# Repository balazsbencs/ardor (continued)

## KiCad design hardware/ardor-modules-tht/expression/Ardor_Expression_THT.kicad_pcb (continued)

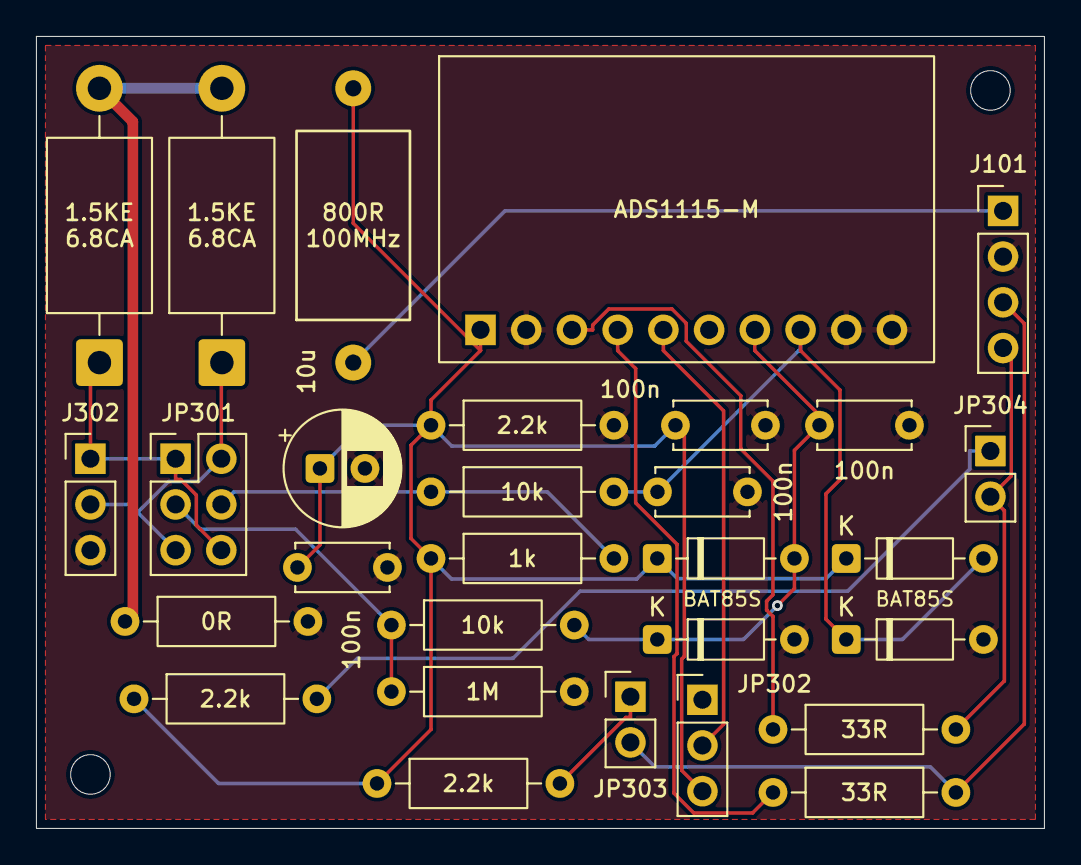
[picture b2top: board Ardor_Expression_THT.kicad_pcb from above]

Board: 2 copper layers, 56.0 x 44.0 mm, 31 parts (0 on the bottom side), 17 nets.

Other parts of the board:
H1, H2: MountingHole_2.2mm_M2

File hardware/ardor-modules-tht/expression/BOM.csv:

Reference,Value,Footprint,Purchasing specification,Assembly
J302,"PASSIVE PEDAL INPUT / EXCITATION
OUTPUT",Connector_PinHeader_2.54mm:PinHeader_1x03_P2.54mm_Vertical,PinHeader_1x03_P2.54mm_Vertical,THT manual
J101,3V3 POWER INPUT + I2C TO HOST,Connector_PinHeader_2.54mm:PinHeader_1x04_P2.54mm_Vertical,PinHeader_1x04_P2.54mm_Vertical,THT manual
JP301,JUMPER ONLY: PEDAL POLARITY,Connector_PinHeader_2.54mm:PinHeader_2x03_P2.54mm_Vertical,PinHeader_2x03_P2.54mm_Vertical,THT manual
FB101,800R@100MHz / WE 7427501,Ardor_THT:Ferrite_WE_7427501_P15.24mm,Wurth Elektronik 7427501,THT manual
C101,10u / 25V polarized,Capacitor_THT:CP_Radial_D6.3mm_P2.50mm,"Radial electrolytic 10uF 25V, D<=6.3mm P2.5mm",THT manual
C102,100n / 50V X7R,Capacitor_THT:C_Disc_D5.0mm_W2.5mm_P5.00mm,"100nF 50V X7R radial, 5mm lead pitch",THT manual
R301,1kR / 1% 0.25W,Resistor_THT:R_Axial_DIN0207_L6.3mm_D2.5mm_P10.16mm_Horizontal,Axial metal film 1kΩ 1% 0.25W,THT manual
R302,10kR / 1% 0.25W,Resistor_THT:R_Axial_DIN0207_L6.3mm_D2.5mm_P10.16mm_Horizontal,Axial metal film 10kΩ 1% 0.25W,THT manual
R303,1MR / 1% 0.25W,Resistor_THT:R_Axial_DIN0207_L6.3mm_D2.5mm_P10.16mm_Horizontal,Axial metal film 1MΩ 1% 0.25W,THT manual
C301,100n / 50V X7R,Capacitor_THT:C_Disc_D5.0mm_W2.5mm_P5.00mm,"100nF 50V X7R radial, 5mm lead pitch",THT manual
R304,10kR / 1% 0.25W,Resistor_THT:R_Axial_DIN0207_L6.3mm_D2.5mm_P10.16mm_Horizontal,Axial metal film 10kΩ 1% 0.25W,THT manual
C302,100n / 50V X7R,Capacitor_THT:C_Disc_D5.0mm_W2.5mm_P5.00mm,"100nF 50V X7R radial, 5mm lead pitch",THT manual
U301,ADS1115-M,Ardor_THT:ADS1115_M_HESTORE_10041798,ADS1115-M (HESTORE 100.417.98),Preassembled module; THT sockets
C303,100n / 50V X7R,Capacitor_THT:C_Disc_D5.0mm_W2.5mm_P5.00mm,"100nF 50V X7R radial, 5mm lead pitch",THT manual
R307,2.2kR / 1% 0.25W,Resistor_THT:R_Axial_DIN0207_L6.3mm_D2.5mm_P10.16mm_Horizontal,Axial metal film 2.2kΩ 1% 0.25W,THT manual
D303,BAT85S,Diode_THT:D_DO-35_SOD27_P7.62mm_Horizontal,Vishay BAT85S-TAP,THT manual
D304,BAT85S,Diode_THT:D_DO-35_SOD27_P7.62mm_Horizontal,Vishay BAT85S-TAP,THT manual
D305,BAT85S,Diode_THT:D_DO-35_SOD27_P7.62mm_Horizontal,Vishay BAT85S-TAP,THT manual
D306,BAT85S,Diode_THT:D_DO-35_SOD27_P7.62mm_Horizontal,Vishay BAT85S-TAP,THT manual
R305,33R / 1% 0.25W,Resistor_THT:R_Axial_DIN0207_L6.3mm_D2.5mm_P10.16mm_Horizontal,Axial metal film 33Ω 1% 0.25W,THT manual
R306,33R / 1% 0.25W,Resistor_THT:R_Axial_DIN0207_L6.3mm_D2.5mm_P10.16mm_Horizontal,Axial metal film 33Ω 1% 0.25W,THT manual
JP302,JUMPER ONLY: ADC ADDRESS,Connector_PinHeader_2.54mm:PinHeader_1x03_P2.54mm_Vertical,PinHeader_1x03_P2.54mm_Vertical,THT manual
JP303,JUMPER ONLY: SDA PULLUP,Connector_PinHeader_2.54mm:PinHeader_1x02_P2.54mm_Vertical,PinHeader_1x02_P2.54mm_Vertical,THT manual
JP304,JUMPER ONLY: SCL PULLUP,Connector_PinHeader_2.54mm:PinHeader_1x02_P2.54mm_Vertical,PinHeader_1x02_P2.54mm_Vertical,THT manual
R308,2.2kR / 1% 0.25W,Resistor_THT:R_Axial_DIN0207_L6.3mm_D2.5mm_P10.16mm_Horizontal,Axial metal film 2.2kΩ 1% 0.25W,THT manual
R309,2.2kR / 1% 0.25W,Resistor_THT:R_Axial_DIN0207_L6.3mm_D2.5mm_P10.16mm_Horizontal,Axial metal film 2.2kΩ 1% 0.25W,THT manual
D301,1.5KE6.8CA,Ardor_THT:D_TVS_DC_1.5KE_P15.24mm,DC Components 1.5KE6.8CA (HESTORE 100.430.71),THT manual
D302,1.5KE6.8CA,Ardor_THT:D_TVS_DC_1.5KE_P15.24mm,DC Components 1.5KE6.8CA (HESTORE 100.430.71),THT manual
R101,0R / 1% 0.25W,Resistor_THT:R_Axial_DIN0207_L6.3mm_D2.5mm_P10.16mm_Horizontal,Axial metal film 0Ω 1% 0.25W,THT manual

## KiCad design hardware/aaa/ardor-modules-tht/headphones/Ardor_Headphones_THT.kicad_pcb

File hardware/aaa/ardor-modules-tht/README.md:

# Ardor hand-assembled function modules — T1

These are alternative KiCad 9 projects for the five [M1 production modules](../ardor-modules/README.md). Order bare PCBs and solder them with an ordinary iron. MIDI, mixer and line-out contain **only through-hole components**. The headphone board uses **one hand-solderable OPA1656ID SOIC-8**, with all supporting components through-hole. Expression uses a **purchased, preassembled ADS1115 breakout**: it contains SMD parts, but the builder only solders headers and sockets. The OPA1656 has exposed leads at 1.27 mm pitch and no underside pad; an ordinary iron and flux are sufficient. No hot-air tool or stencil is required.

| Project | PCB dimensions | Regulated supply budget | Assembly / differences from M1 |
|---|---|---|---|
| [MIDI input](midi-in/README.md) | 85 × 70 mm | 5 V / 10 mA + 3.3 V / 5 mA | DIP H11L1M; axial protection/filter parts |
| [Expression](expression/README.md) | 110 × 85 mm | 3.3 V / 15 mA | Socketed Adafruit 1085 **STEMMA QT revision**; same ADS1115 software |
| [Stereo/mono mixer](mixer/README.md) | 100 × 75 mm | 5 V / 10 mA | Socketed MCP6022-I/P; bipolar coupling capacitors |
| [Line output](line-out/README.md) | 115 × 85 mm | 5 V / 50 mA | MCP6022-I/P, through-hole relay, 2N3904 driver |
| [Stereo headphones](headphones/README.md) | 96 × 84 mm | 5 V / 150 mA | One OPA1656ID SOIC-8, THT supporting parts, DPDT relay mute |

All host and panel **connector pin assignments are the same as M1**. The larger boards and mounting holes are not mechanically interchangeable with M1. Each project has its own schematic, routed PCB, local libraries, manual BOM, connector guide, review drawings and bare-board Gerber/drill ZIP. Each module operates independently with an external host/audio source and the listed supplies. No carrier board or other Ardor module is required.

## Build choices

- Use 1% 0.25 W axial resistors, formed to 10.16 mm lead spacing, except headphone feedback resistors R651/R652: stand these upright at 2.54 mm pitch with short folded leads. R101 may be a wire link.
- On the headphone board, solder and inspect the OPA1656 SOIC-8 first; no IC socket or adapter is used. On the other boards, solder DIP sockets before fitting ICs. Match the IC notch to the socket and PCB pin-1 marking. The MIDI H11L1M uses a six-pin DIP footprint; an optional 7.62 mm-wide socket fits it.
- Use the capacitor dimensions and lead pitch in each BOM. The audio coupling capacitors marked **BIPOLAR** must be nonpolar electrolytics; ordinary polarized electrolytics are not substitutes. Polarized radial capacitors have pin 1 = positive and a `+` on the PCB. The can's stripe indicates negative.
- Use **bidirectional** DC Components **1.5KE6.8CA** protection diodes ([HESTORE 100.430.71](https://www.hestore.hu/prod_10043071.html)), formed to **15.24 mm** lead spacing. Either orientation is valid. MIDI D203/D204 retain **SA24CA-E3/54 at 10.16 mm pitch** for their higher-voltage protection function; do not fit 1.5KE6.8CA there. The `CA` suffix matters. Small-signal 1N4148 and BAT85S diodes are polarized: their band goes to the cathode, footprint pad 1.
- Filter beads are Würth 7427501 axial parts, formed to 15.24 mm spacing. Their RF characteristics and the axial TVS capacitance differ from M1; EMC/ESD equivalence is not claimed.
- Line/headphone enable drives a transistor base through 470 Ω. The host must source approximately **5 mA at 3.3 V HIGH**, rather than drive only a MOSFET gate. LOW or disconnected keeps the relay muted. Check the GPIO's drive capability.
- Fit standard 2.54 mm headers; panel DIN/TRS/TS sockets remain connected by wires. Read the module's pin table before wiring: different module types do not share a universal power pinout.

## Headphone tradeoff

The headphone board uses a modern dual OPA1656 audio op amp as the agreed hand-solderable SMD exception. It operates from regulated 5 V ±5% in an inverting circuit with nominal unloaded gain −0.5; both channels invert together. Its inputs stay at the filtered 2.5 V reference because the common-mode input range is restricted near the positive supply. Local feedback uses upright THT 10 kΩ resistors and 100 pF C0G capacitors. A 100 nF THT bypass sits close to U601. The remaining parts are THT.

Two 10 Ω output resistors sit outside the feedback loops, before the 470 µF DC-blocking capacitors. Calculated midband gain into 32 Ω is about −0.378, approximately 4.5 mW/channel for 1 Vrms input. This preserves the modest output level of the DIY alternative; it is not a measured clean-power rating. Use 32–300 Ω headphones, a source no greater than 1 Vrms, and begin at low host volume. Clean output, noise, cable-load stability and startup/switching transients remain bench-test items.
**Keep HP_ENABLE LOW for at least five seconds after the supply and audio are stable.** The 1 kΩ bleeders charge the output capacitors while the relay grounds the panel outputs. The board has no automatic timer: the host must provide this delay and mute before power-down. M1's timing may need adjustment. This relay mutes the output; it does not shut down the amplifiers or save their idle current.

## Files and validation

Open the `.kicad_pro` in the desired folder. Use `BOM.csv` plus `assembly/accessories.csv` for manual shopping and the ZIP under `assembly/` for a bare PCB order. Do not use M1's SMT BOM/CPL for these boards. Front silkscreen identifies every builder-fitted part; back silkscreen provides connector numbers and wiring legends. Native schematic PDFs and front/back/assembly views are under `review/`.

[Printable assembly overview](review/module-overview.pdf) · [All five schematics](review/schematics.pdf)

These are **unbuilt engineering prototypes**. CAD checks establish connectivity, geometry and the documented hand-assembly package choices; they do not establish measured audio quality, ESD performance or startup behavior. Each module guide includes commissioning steps. See [engineering review](review/REVIEW.md), [validation summary](review/validation-summary.json), [design regeneration](design/README.md) and [component sources and substitutions](SOURCES.md).

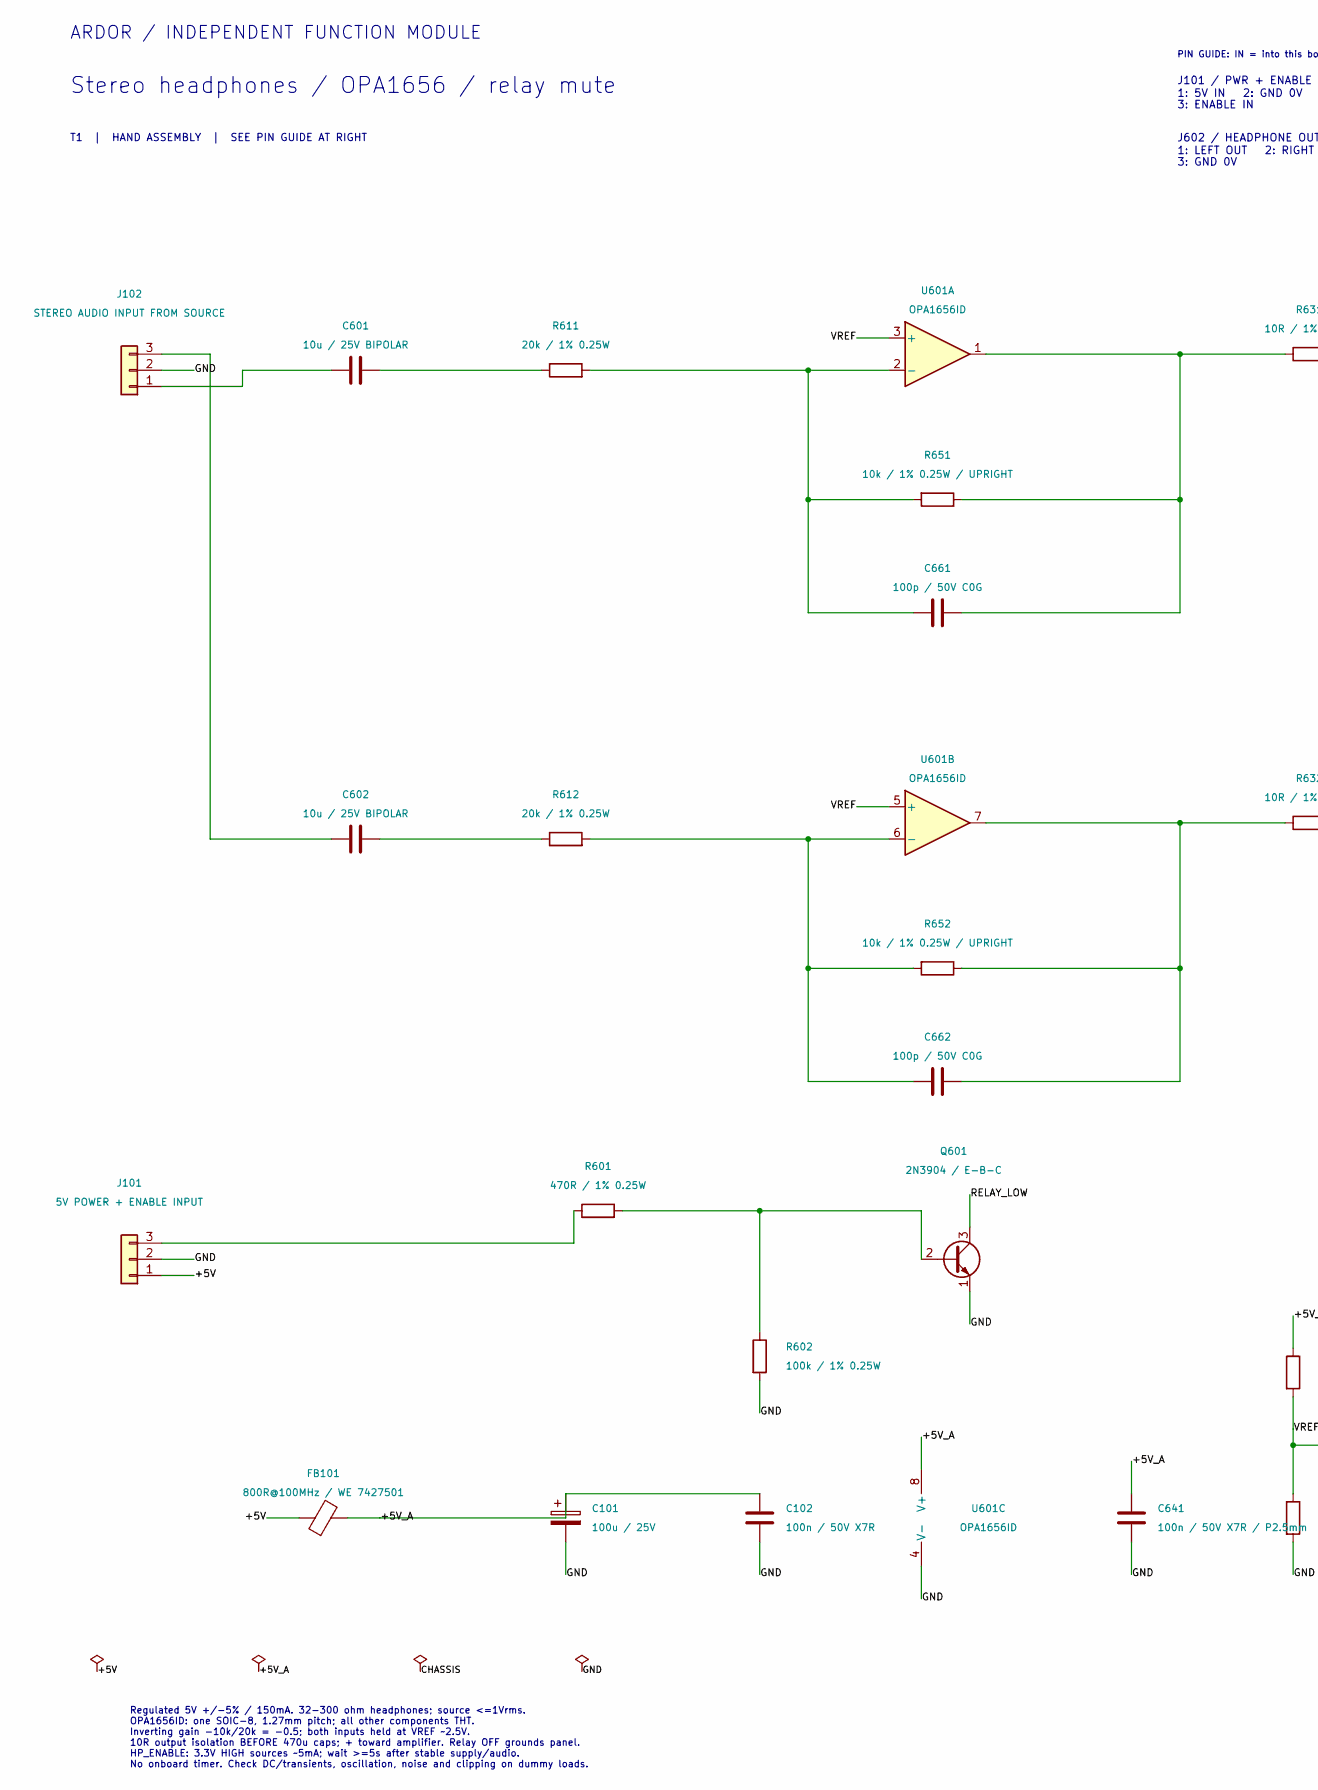
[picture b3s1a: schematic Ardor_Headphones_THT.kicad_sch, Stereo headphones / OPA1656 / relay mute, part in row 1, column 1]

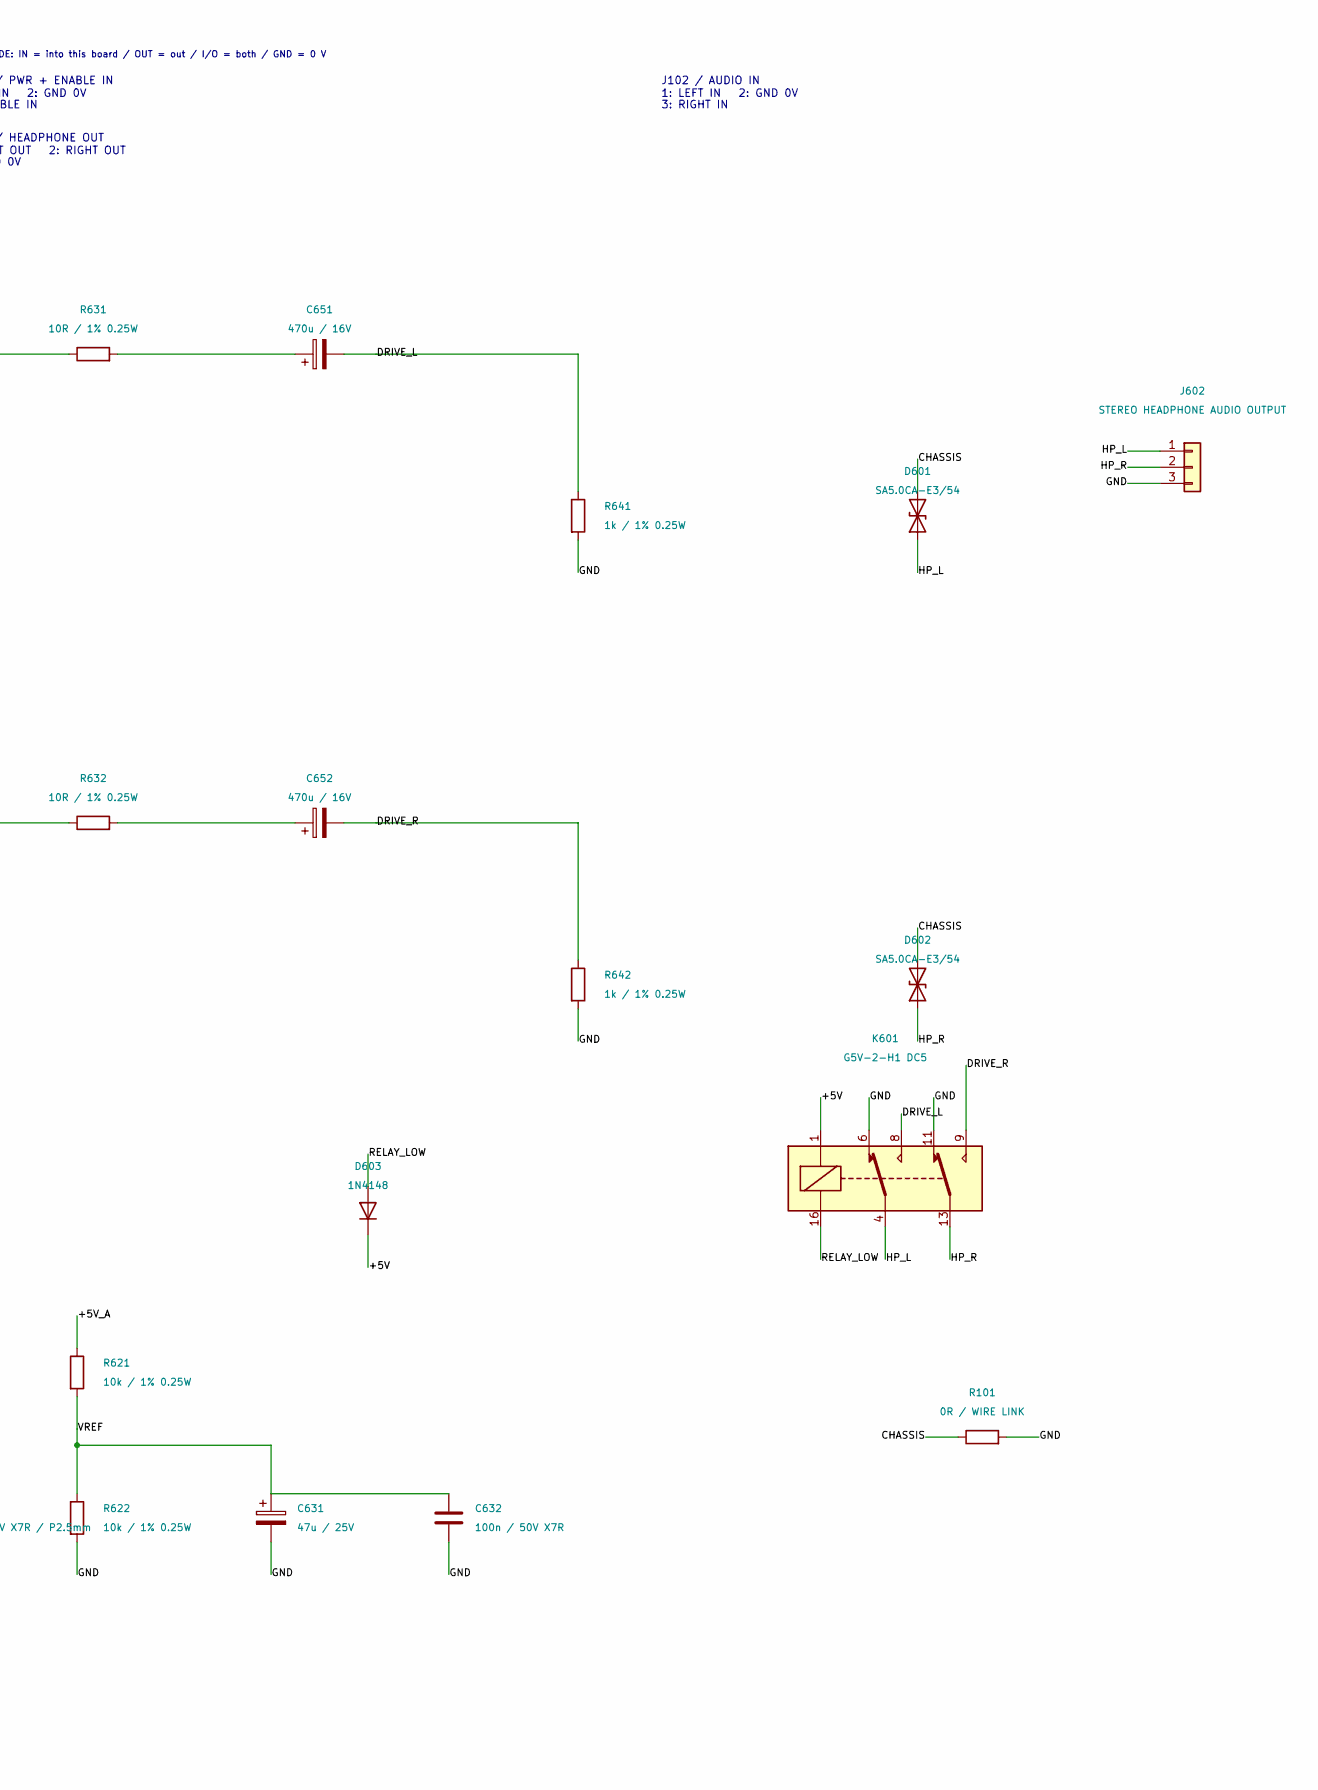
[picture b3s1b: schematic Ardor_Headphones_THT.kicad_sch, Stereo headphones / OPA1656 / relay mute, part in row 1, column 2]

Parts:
C101: 100u / 25V; CP_Radial_D6.3mm_P2.50mm; MPN 100u / 25V
C102, C632: 100n / 50V X7R; C_Disc_D5.0mm_W2.5mm_P5.00mm; MPN 100n / 50V X7R
C601, C602: 10u / 25V BIPOLAR; CP_Bipolar_D6.3mm_P2.50mm; MPN Nichicon UES1E100MDM
C631: 47u / 25V; CP_Radial_D6.3mm_P2.50mm; MPN 47u / 25V
C641: 100n / 50V X7R / P2.5mm; C_Disc_D3.8mm_W2.6mm_P2.50mm; MPN 100nF 50V X7R radial, D<=3.8mm W<=2.6mm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
C651, C652: 470u / 16V; CP_Radial_D8.0mm_P3.50mm; MPN 470u / 16V
C661, C662: 100p / 50V C0G; C_Disc_D5.0mm_W2.5mm_P5.00mm; MPN 100p / 50V C0G
D601, D602: SA5.0CA-E3/54; D_DO-15_P10.16mm_Horizontal; MPN Vishay SA5.0CA-E3/54
D603: 1N4148; D_DO-35_SOD27_P7.62mm_Horizontal; MPN Vishay 1N4148-TAP
FB101: 800R@100MHz / WE 7427501; Ferrite_WE_7427501_P15.24mm; MPN Wurth Elektronik 7427501
J101: 5V POWER + ENABLE INPUT; PinHeader_1x03_P2.54mm_Vertical; MPN PinHeader_1x03_P2.54mm_Vertical
J102: STEREO AUDIO INPUT FROM SOURCE; PinHeader_1x03_P2.54mm_Vertical; MPN PinHeader_1x03_P2.54mm_Vertical
J602: STEREO HEADPHONE AUDIO OUTPUT; PinHeader_1x03_P2.54mm_Vertical; MPN PinHeader_1x03_P2.54mm_Vertical
K601: G5V-2-H1 DC5; Relay_DPDT_Omron_G5V-2; MPN Omron G5V-2-H1 DC5
Q601: 2N3904 / E-B-C; TO-92_Inline_Wide; MPN onsemi 2N3904BU
R101: 0R / WIRE LINK; R_Axial_DIN0207_L6.3mm_D2.5mm_P10.16mm_Horizontal; MPN 0R / WIRE LINK
R601: 470R / 1% 0.25W; R_Axial_DIN0207_L6.3mm_D2.5mm_P10.16mm_Horizontal; MPN 470R / 1% 0.25W
R602: 100k / 1% 0.25W; R_Axial_DIN0207_L6.3mm_D2.5mm_P10.16mm_Horizontal; MPN 100k / 1% 0.25W
R611, R612: 20k / 1% 0.25W; R_Axial_DIN0207_L6.3mm_D2.5mm_P10.16mm_Horizontal; MPN 20k / 1% 0.25W
R621, R622: 10k / 1% 0.25W; R_Axial_DIN0207_L6.3mm_D2.5mm_P10.16mm_Horizontal; MPN 10k / 1% 0.25W
R631, R632: 10R / 1% 0.25W; R_Axial_DIN0207_L6.3mm_D2.5mm_P10.16mm_Horizontal; MPN 10R / 1% 0.25W
R641, R642: 1k / 1% 0.25W; R_Axial_DIN0207_L6.3mm_D2.5mm_P10.16mm_Horizontal; MPN 1k / 1% 0.25W
R651, R652: 10k / 1% 0.25W / UPRIGHT; R_Axial_DIN0207_L6.3mm_D2.5mm_P2.54mm_Vertical; MPN 10k / 1% 0.25W / UPRIGHT
U601: OPA1656ID; SOIC-8_3.9x4.9mm_P1.27mm; MPN Texas Instruments OPA1656ID

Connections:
/+5V: D603.1 (K), FB101.1, J101.1, K601.1
/+5V_A: C101.1, C102.1, C641.1, FB101.2, R621.1, U601.8 (V+)
/CHASSIS: D601.2 (A2), D602.2 (A2), R101.1
/DRIVE_L: C651.2, K601.8, R641.1
/DRIVE_R: C652.2, K601.9, R642.1
/GND: C101.2, C102.2, C631.2, C632.2, C641.2, J101.2, J102.2, J602.3, K601.6, K601.11, Q601.1 (E), R101.2, R602.2, R622.2, R641.2, R642.2, U601.4 (V-)
/HP_L: D601.1 (A1), J602.1, K601.4
/HP_R: D602.1 (A1), J602.2, K601.13
/RELAY_LOW: D603.2 (A), K601.16, Q601.3 (C)
/VREF: C631.1, C632.1, R621.2, R622.1, U601.3 (+), U601.5 (+)
unnamed: C601.2, R611.1
unnamed: C602.2, R612.1
unnamed: C651.1, R631.2
unnamed: C652.1, R632.2
unnamed: C661.1, R631.1, R651.1, U601.1
unnamed: C662.1, R632.1, R652.1, U601.7
unnamed: J101.3, R601.1
unnamed: C601.1, J102.1
unnamed: C602.1, J102.3
unnamed: Q601.2 (B), R601.2, R602.1
unnamed: C661.2, R611.2, R651.2, U601.2 (-)
unnamed: C662.2, R612.2, R652.2, U601.6 (-)

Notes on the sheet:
ARDOR / INDEPENDENT FUNCTION MODULE
Stereo headphones / OPA1656 / relay mute
T1 | HAND ASSEMBLY | SEE PIN GUIDE AT RIGHT
Regulated 5V +/-5% / 150mA. 32-300 ohm headphones; source <=1Vrms. OPA1656ID: one SOIC-8, 1.27mm pitch; all other components THT. Inverting gain -10k/20k = -0.5; both inputs held at VREF ~2.5V. 10R output isolation BEFORE 470u caps; + toward amplifier. Relay OFF grounds panel. HP_ENABLE: 3.3V HIGH 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
PIN GUIDE: IN = into this board / OUT = out / I/O = both / GND = 0 V
J101 / PWR + ENABLE IN
1: 5V IN 2: GND 0V
3: ENABLE IN
J102 / AUDIO IN
1: LEFT IN 2: GND 0V
3: RIGHT IN
J602 / HEADPHONE OUT
1: LEFT OUT 2: RIGHT OUT
3: GND 0V

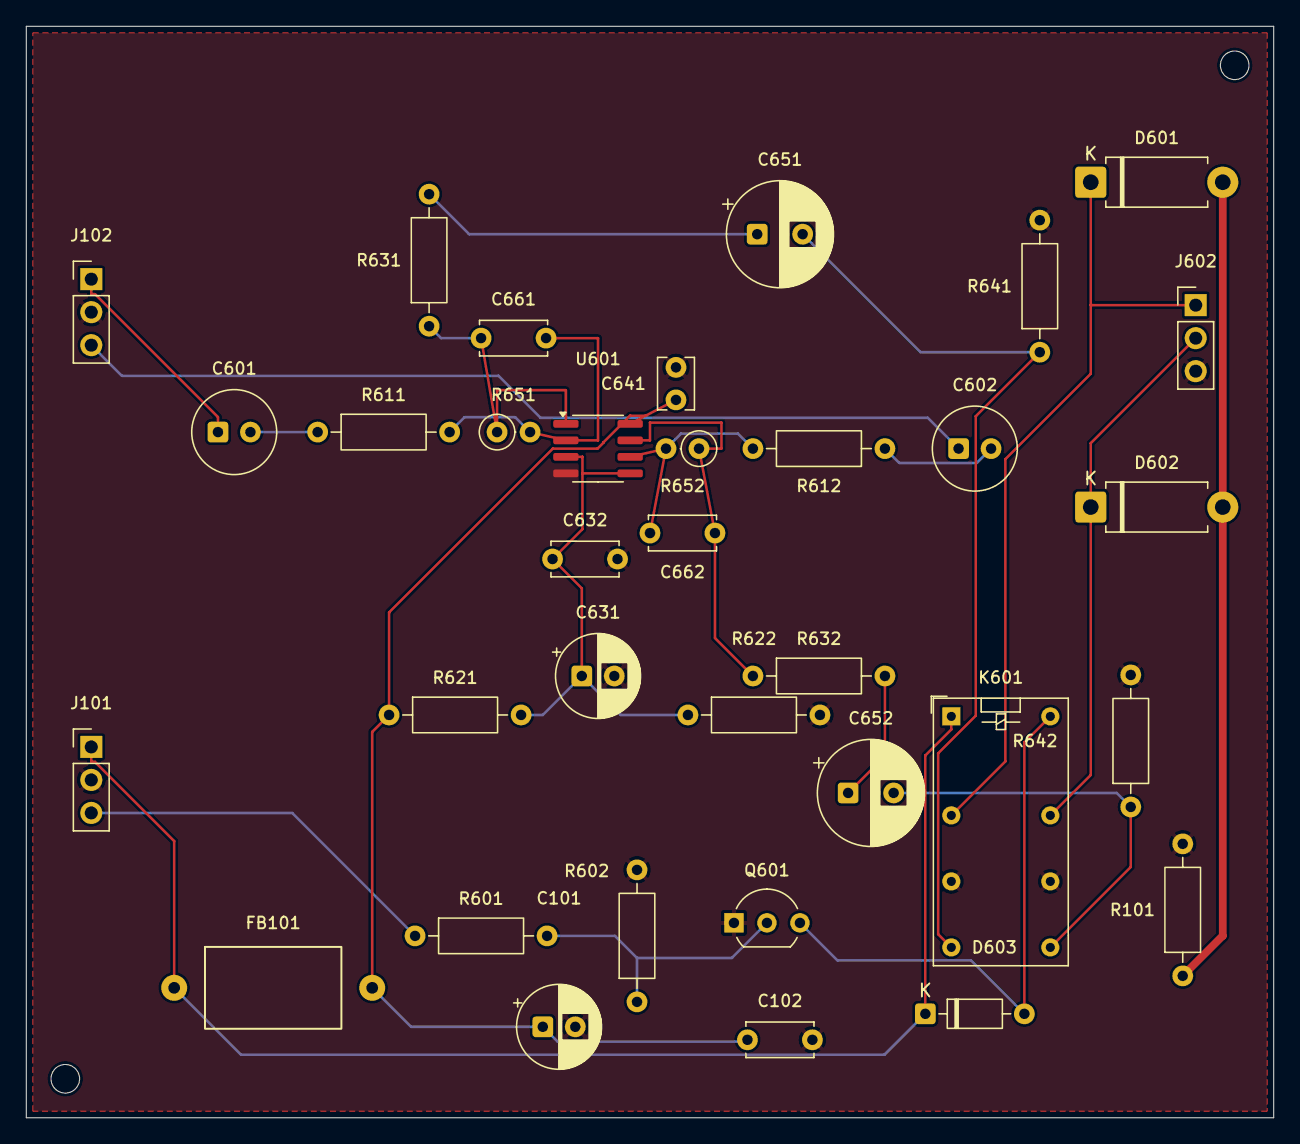
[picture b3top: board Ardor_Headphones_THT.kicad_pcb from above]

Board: 2 copper layers, 96.0 x 84.0 mm, 36 parts (0 on the bottom side), 22 nets.

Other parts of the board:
H1, H2: MountingHole_2.2mm_M2

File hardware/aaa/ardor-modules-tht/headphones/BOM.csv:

Reference,Value,Footprint,Purchasing specification,Assembly
J102,STEREO AUDIO INPUT FROM SOURCE,Connector_PinHeader_2.54mm:PinHeader_1x03_P2.54mm_Vertical,PinHeader_1x03_P2.54mm_Vertical,THT manual
J101,5V POWER + ENABLE INPUT,Connector_PinHeader_2.54mm:PinHeader_1x03_P2.54mm_Vertical,PinHeader_1x03_P2.54mm_Vertical,THT manual
J602,STEREO HEADPHONE AUDIO OUTPUT,Connector_PinHeader_2.54mm:PinHeader_1x03_P2.54mm_Vertical,PinHeader_1x03_P2.54mm_Vertical,THT manual
FB101,800R@100MHz / WE 7427501,Ardor_THT:Ferrite_WE_7427501_P15.24mm,Wurth Elektronik 7427501,THT manual
C101,100u / 25V,Capacitor_THT:CP_Radial_D6.3mm_P2.50mm,100u / 25V,THT manual
C102,100n / 50V X7R,Capacitor_THT:C_Disc_D5.0mm_W2.5mm_P5.00mm,100n / 50V X7R,THT manual
C601,10u / 25V BIPOLAR,Ardor_THT:CP_Bipolar_D6.3mm_P2.50mm,Nichicon UES1E100MDM,THT manual
R611,20k / 1% 0.25W,Resistor_THT:R_Axial_DIN0207_L6.3mm_D2.5mm_P10.16mm_Horizontal,20k / 1% 0.25W,THT manual
U601,OPA1656ID,Package_SO:SOIC-8_3.9x4.9mm_P1.27mm,Texas Instruments OPA1656ID,SMD manual / SOIC-8 1.27mm pitch
R651,10k / 1% 0.25W / UPRIGHT,Resistor_THT:R_Axial_DIN0207_L6.3mm_D2.5mm_P2.54mm_Vertical,10k / 1% 0.25W / UPRIGHT,THT manual
C661,100p / 50V C0G,Capacitor_THT:C_Disc_D5.0mm_W2.5mm_P5.00mm,100p / 50V C0G,THT manual
R631,10R / 1% 0.25W,Resistor_THT:R_Axial_DIN0207_L6.3mm_D2.5mm_P10.16mm_Horizontal,10R / 1% 0.25W,THT manual
C651,470u / 16V,Capacitor_THT:CP_Radial_D8.0mm_P3.50mm,470u / 16V,THT manual
R641,1k / 1% 0.25W,Resistor_THT:R_Axial_DIN0207_L6.3mm_D2.5mm_P10.16mm_Horizontal,1k / 1% 0.25W,THT manual
D601,1.5KE6.8CA,Ardor_THT:D_TVS_DC_1.5KE_P15.24mm,DC Components 1.5KE6.8CA (HESTORE 100.430.71),THT manual
C602,10u / 25V BIPOLAR,Ardor_THT:CP_Bipolar_D6.3mm_P2.50mm,Nichicon UES1E100MDM,THT manual
R612,20k / 1% 0.25W,Resistor_THT:R_Axial_DIN0207_L6.3mm_D2.5mm_P10.16mm_Horizontal,20k / 1% 0.25W,THT manual
R652,10k / 1% 0.25W / UPRIGHT,Resistor_THT:R_Axial_DIN0207_L6.3mm_D2.5mm_P2.54mm_Vertical,10k / 1% 0.25W / UPRIGHT,THT manual
C662,100p / 50V C0G,Capacitor_THT:C_Disc_D5.0mm_W2.5mm_P5.00mm,100p / 50V C0G,THT manual
R632,10R / 1% 0.25W,Resistor_THT:R_Axial_DIN0207_L6.3mm_D2.5mm_P10.16mm_Horizontal,10R / 1% 0.25W,THT manual
C652,470u / 16V,Capacitor_THT:CP_Radial_D8.0mm_P3.50mm,470u / 16V,THT manual
R642,1k / 1% 0.25W,Resistor_THT:R_Axial_DIN0207_L6.3mm_D2.5mm_P10.16mm_Horizontal,1k / 1% 0.25W,THT manual
D602,1.5KE6.8CA,Ardor_THT:D_TVS_DC_1.5KE_P15.24mm,DC Components 1.5KE6.8CA (HESTORE 100.430.71),THT manual
C641,100n / 50V X7R / P2.5mm,Capacitor_THT:C_Disc_D3.8mm_W2.6mm_P2.50mm,"100nF 50V X7R radial, D<=3.8mm W<=2.6mm P2.5mm",THT manual
R621,10k / 1% 0.25W,Resistor_THT:R_Axial_DIN0207_L6.3mm_D2.5mm_P10.16mm_Horizontal,10k / 1% 0.25W,THT manual
R622,10k / 1% 0.25W,Resistor_THT:R_Axial_DIN0207_L6.3mm_D2.5mm_P10.16mm_Horizontal,10k / 1% 0.25W,THT manual
C631,47u / 25V,Capacitor_THT:CP_Radial_D6.3mm_P2.50mm,47u / 25V,THT manual
C632,100n / 50V X7R,Capacitor_THT:C_Disc_D5.0mm_W2.5mm_P5.00mm,100n / 50V X7R,THT manual
K601,G5V-2-H1 DC5,Relay_THT:Relay_DPDT_Omron_G5V-2,Omron G5V-2-H1 DC5,THT manual
Q601,2N3904 / E-B-C,Package_TO_SOT_THT:TO-92_Inline_Wide,onsemi 2N3904BU,THT manual
R601,470R / 1% 0.25W,Resistor_THT:R_Axial_DIN0207_L6.3mm_D2.5mm_P10.16mm_Horizontal,470R / 1% 0.25W,THT manual
R602,100k / 1% 0.25W,Resistor_THT:R_Axial_DIN0207_L6.3mm_D2.5mm_P10.16mm_Horizontal,100k / 1% 0.25W,THT manual
D603,1N4148,Diode_THT:D_DO-35_SOD27_P7.62mm_Horizontal,Vishay 1N4148-TAP,THT manual
R101,0R / WIRE LINK,Resistor_THT:R_Axial_DIN0207_L6.3mm_D2.5mm_P10.16mm_Horizontal,0R / WIRE LINK,THT manual

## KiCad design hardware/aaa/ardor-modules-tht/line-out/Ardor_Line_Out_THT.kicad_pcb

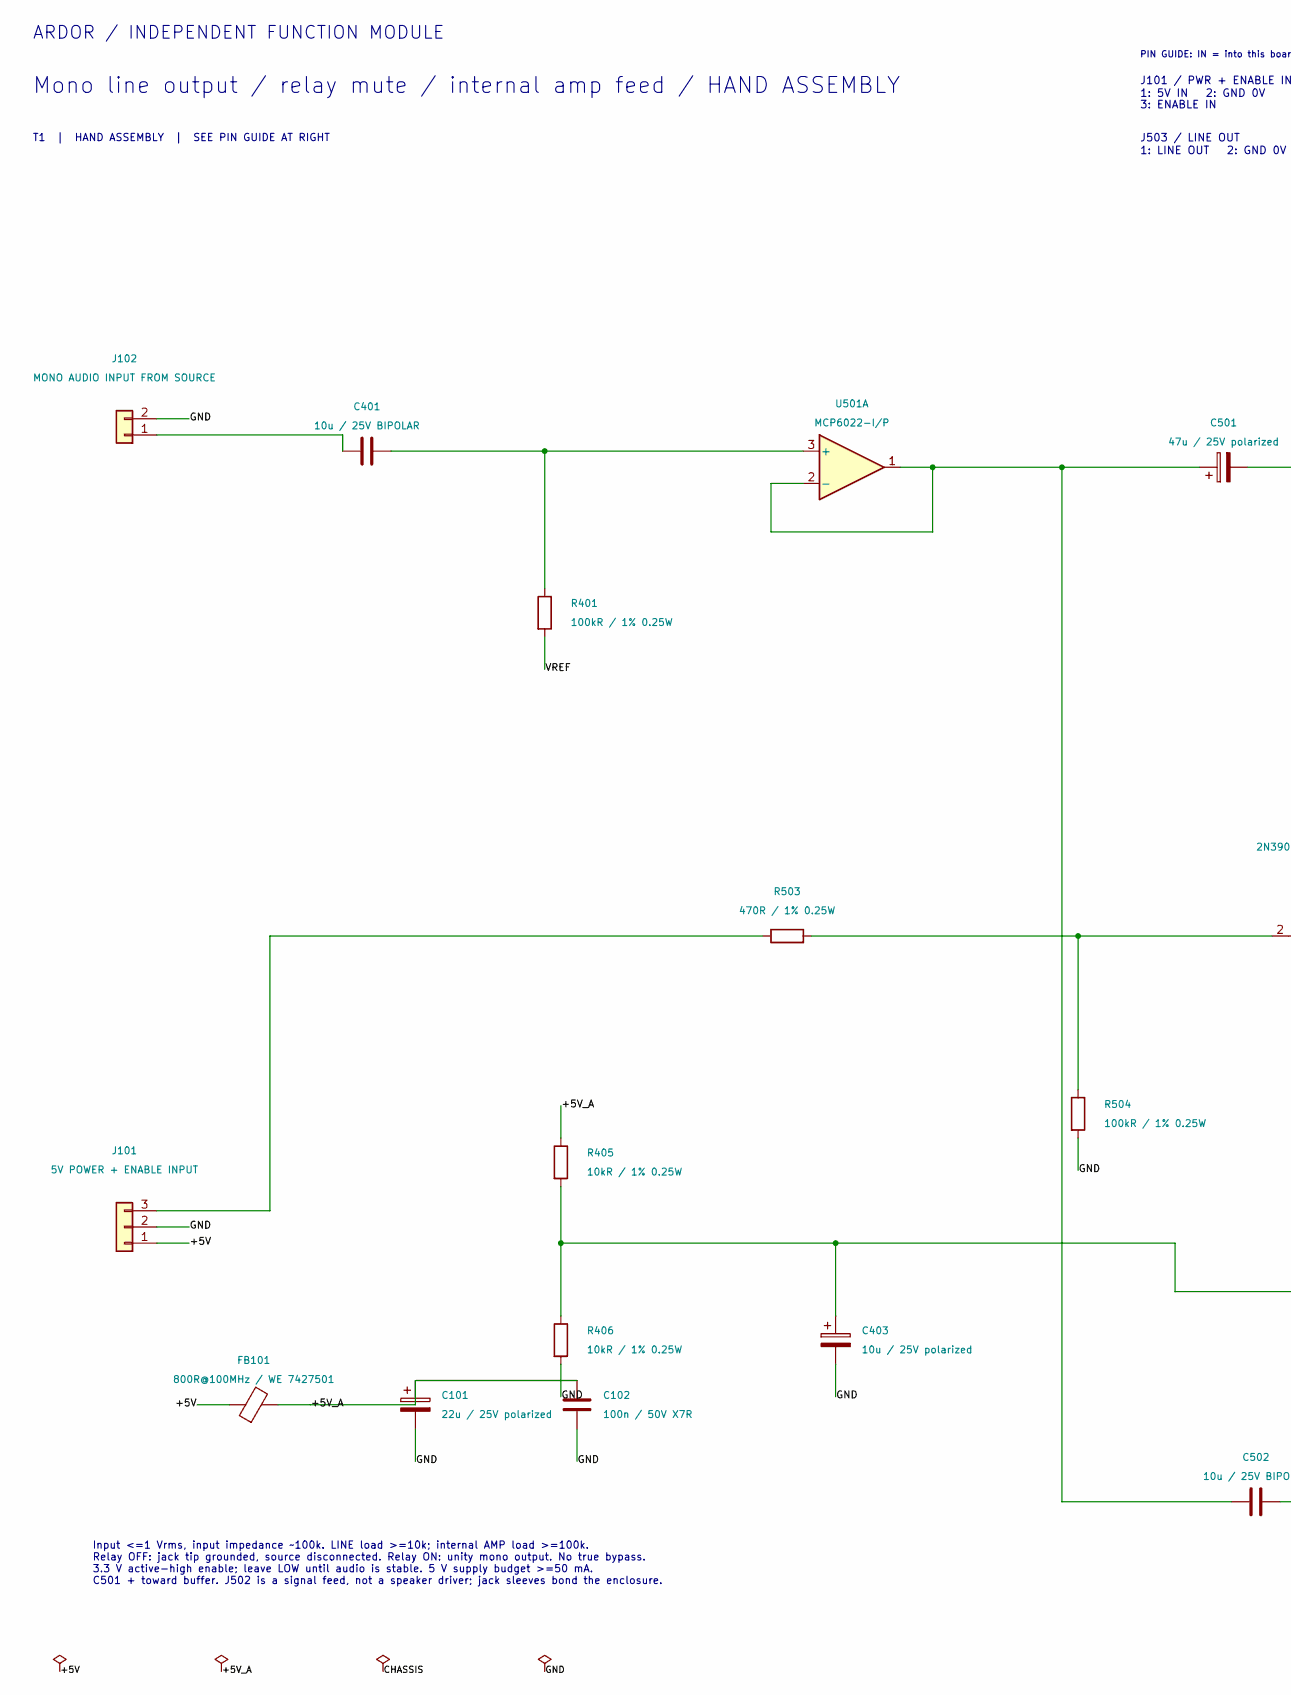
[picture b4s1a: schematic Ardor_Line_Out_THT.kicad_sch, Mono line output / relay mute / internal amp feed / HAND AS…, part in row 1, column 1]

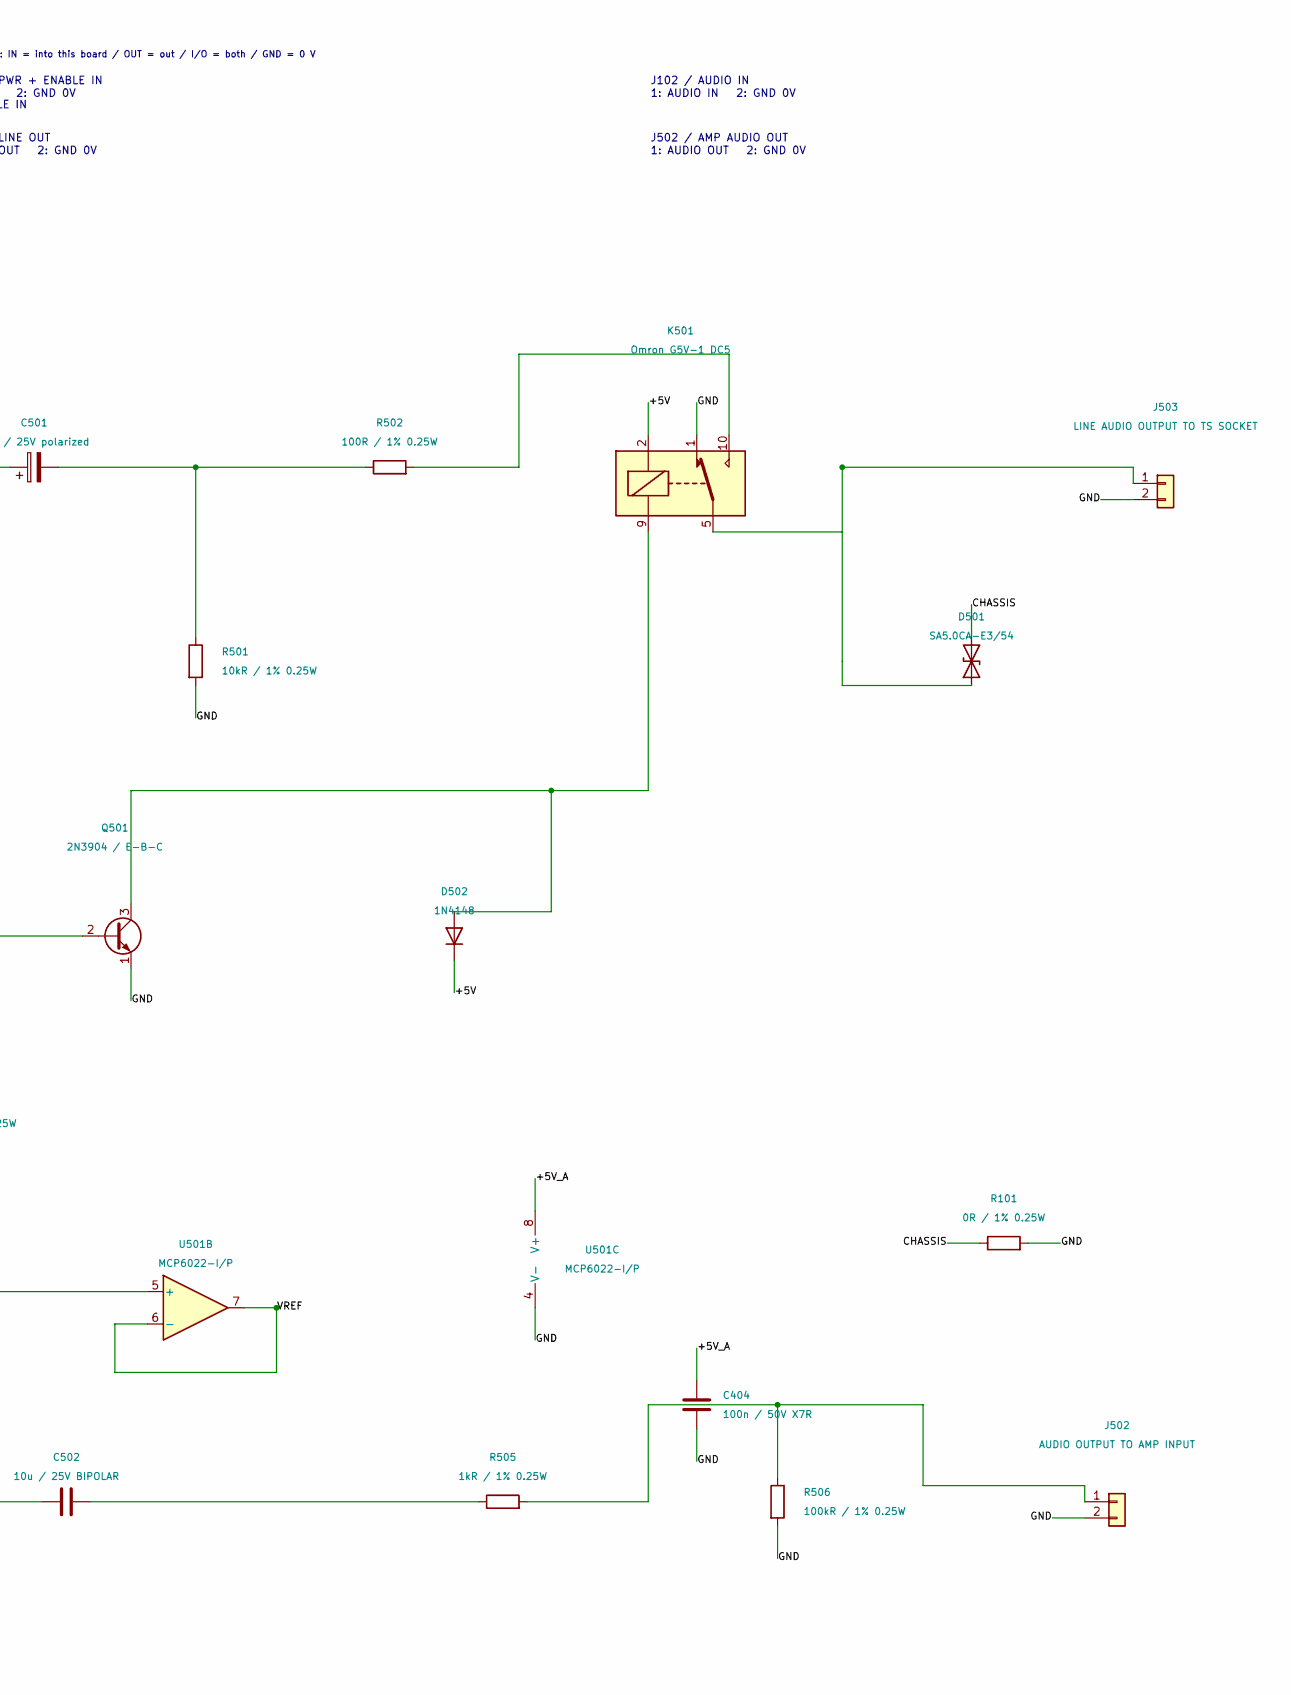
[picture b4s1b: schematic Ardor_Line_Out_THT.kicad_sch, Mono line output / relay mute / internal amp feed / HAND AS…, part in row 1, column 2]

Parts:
C101: 22u / 25V polarized; CP_Radial_D6.3mm_P2.50mm; MPN Radial electrolytic 22uF 25V, D<=6.3mm 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
C102, C404: 100n / 50V X7R; C_Disc_D5.0mm_W2.5mm_P5.00mm; MPN 100nF 50V X7R radial, 5mm lead pitch
C401, C502: 10u / 25V BIPOLAR; CP_Bipolar_D6.3mm_P2.50mm; MPN Nichicon UES1E100MDM
C403: 10u / 25V polarized; CP_Radial_D6.3mm_P2.50mm; MPN Radial electrolytic 10uF 25V, D<=6.3mm 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
C501: 47u / 25V polarized; CP_Radial_D6.3mm_P2.50mm; MPN Radial electrolytic 47uF 25V, D<=6.3mm 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
D501: SA5.0CA-E3/54; D_DO-15_P10.16mm_Horizontal; MPN Vishay SA5.0CA-E3/54
D502: 1N4148; D_DO-35_SOD27_P7.62mm_Horizontal; MPN Vishay 1N4148-TAP
FB101: 800R@100MHz / WE 7427501; Ferrite_WE_7427501_P15.24mm; MPN Wurth Elektronik 7427501
J101: 5V POWER + ENABLE INPUT; PinHeader_1x03_P2.54mm_Vertical; MPN PinHeader_1x03_P2.54mm_Vertical
J102: MONO AUDIO INPUT FROM SOURCE; PinHeader_1x02_P2.54mm_Vertical; MPN PinHeader_1x02_P2.54mm_Vertical
J502: AUDIO OUTPUT TO AMP INPUT; PinHeader_1x02_P2.54mm_Vertical; MPN PinHeader_1x02_P2.54mm_Vertical
J503: LINE AUDIO OUTPUT TO TS SOCKET; PinHeader_1x02_P2.54mm_Vertical; MPN PinHeader_1x02_P2.54mm_Vertical
K501: Omron G5V-1 DC5; Relay_SPDT_Omron_G5V-1; MPN Omron G5V-1 DC5
Q501: 2N3904 / E-B-C; TO-92_Inline_Wide; MPN onsemi 2N3904BU
R101: 0R / 1% 0.25W; R_Axial_DIN0207_L6.3mm_D2.5mm_P10.16mm_Horizontal; MPN Axial metal film 0Ω 1% 0.25W
R401, R504, R506: 100kR / 1% 0.25W; R_Axial_DIN0207_L6.3mm_D2.5mm_P10.16mm_Horizontal; MPN Axial metal film 100kΩ 1% 0.25W
R405, R406, R501: 10kR / 1% 0.25W; R_Axial_DIN0207_L6.3mm_D2.5mm_P10.16mm_Horizontal; MPN Axial metal film 10kΩ 1% 0.25W
R502: 100R / 1% 0.25W; R_Axial_DIN0207_L6.3mm_D2.5mm_P10.16mm_Horizontal; MPN Axial metal film 100Ω 1% 0.25W
R503: 470R / 1% 0.25W; R_Axial_DIN0207_L6.3mm_D2.5mm_P10.16mm_Horizontal; MPN Axial metal film 470Ω 1% 0.25W
R505: 1kR / 1% 0.25W; R_Axial_DIN0207_L6.3mm_D2.5mm_P10.16mm_Horizontal; MPN Axial metal film 1kΩ 1% 0.25W
U501: MCP6022-I/P; DIP-8_W7.62mm_Socket; MPN Microchip MCP6022-I/P

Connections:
/+5V: D502.1 (K), FB101.1, J101.1, K501.2
/+5V_A: C101.1, C102.1, C404.1, FB101.2, R405.1, U501.8 (V+)
/CHASSIS: D501.2 (A2), R101.1
/GND: C101.2, C102.2, C403.2, C404.2, J101.2, J102.2, J502.2, J503.2, K501.1, Q501.1 (E), R101.2, R406.2, R501.2, R504.2, R506.2, U501.4 (V-)
/VREF: R401.2, U501.6 (-), U501.7
unnamed: C501.2, R501.1, R502.1
unnamed: C502.2, R505.1
unnamed: D501.1 (A1), J503.1, K501.5, K501.6
unnamed: D502.2 (A), K501.9, Q501.3 (C)
unnamed: J101.3, R503.1
unnamed: C401.1, J102.1
unnamed: J502.1, R505.2, R506.1
unnamed: K501.10, R502.2
unnamed: Q501.2 (B), R503.2, R504.1
unnamed: C401.2, R401.1, U501.3 (+)
unnamed: C501.1, C502.1, U501.1, U501.2 (-)
unnamed: C403.1, R405.2, R406.1, U501.5 (+)

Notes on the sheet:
ARDOR / INDEPENDENT FUNCTION MODULE
Mono line output / relay mute / internal amp feed / HAND ASSEMBLY
T1 | HAND ASSEMBLY | SEE PIN GUIDE AT RIGHT
Input <=1 Vrms, input impedance ~100k. LINE load >=10k; internal AMP load >=100k. Relay OFF: jack tip grounded, source disconnected. Relay ON: unity mono output. No true bypass. 3.3 V active-high enable; leave LOW until audio is stable. 5 V supply budget >=50 mA. C501 + toward buffer. J502 is a sig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
PIN GUIDE: IN = into this board / OUT = out / I/O = both / GND = 0 V
J101 / PWR + ENABLE IN
1: 5V IN 2: GND 0V
3: ENABLE IN
J102 / AUDIO IN
1: AUDIO IN 2: GND 0V
J503 / LINE OUT
1: LINE OUT 2: GND 0V
J502 / AMP AUDIO OUT
1: AUDIO OUT 2: GND 0V
